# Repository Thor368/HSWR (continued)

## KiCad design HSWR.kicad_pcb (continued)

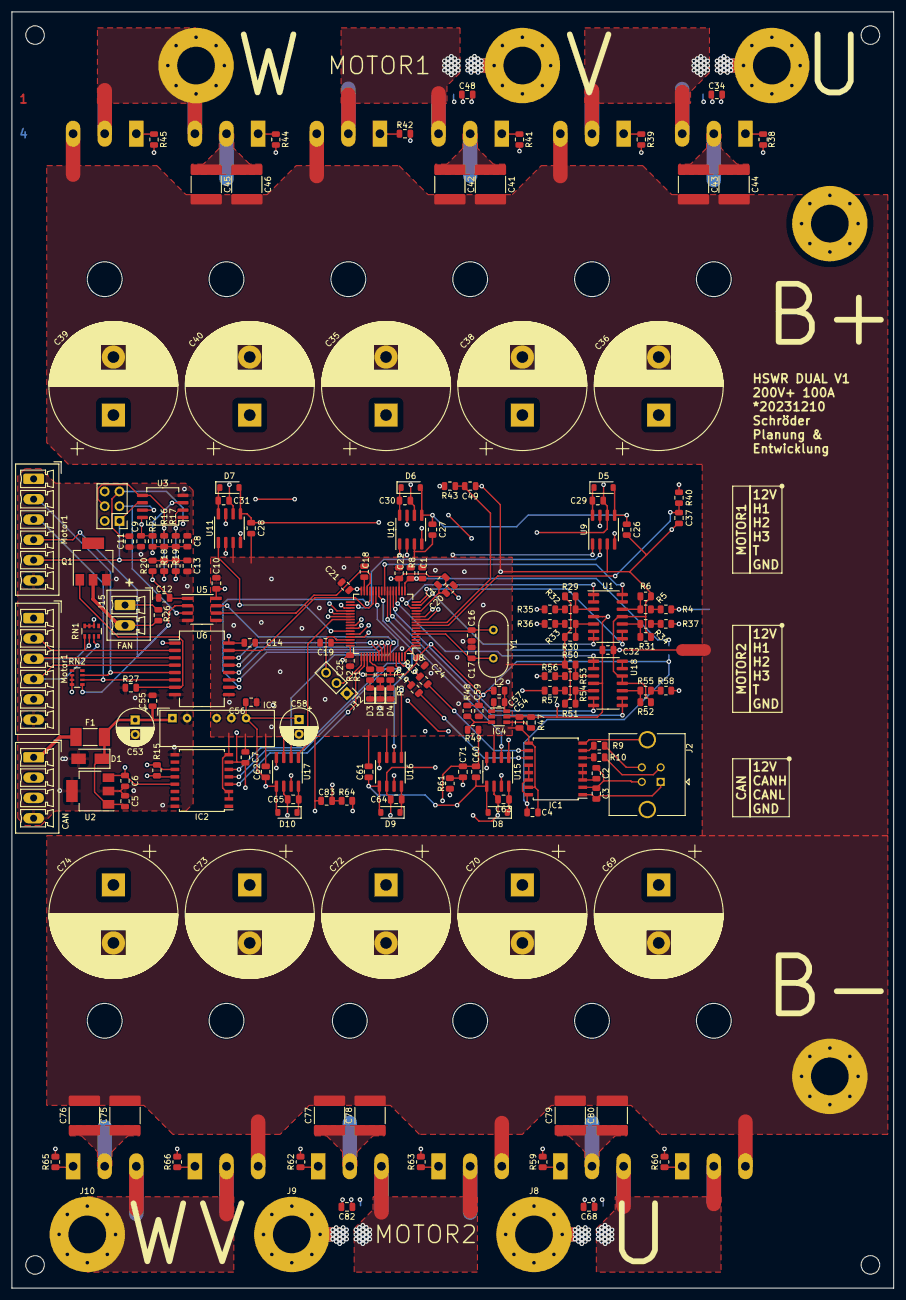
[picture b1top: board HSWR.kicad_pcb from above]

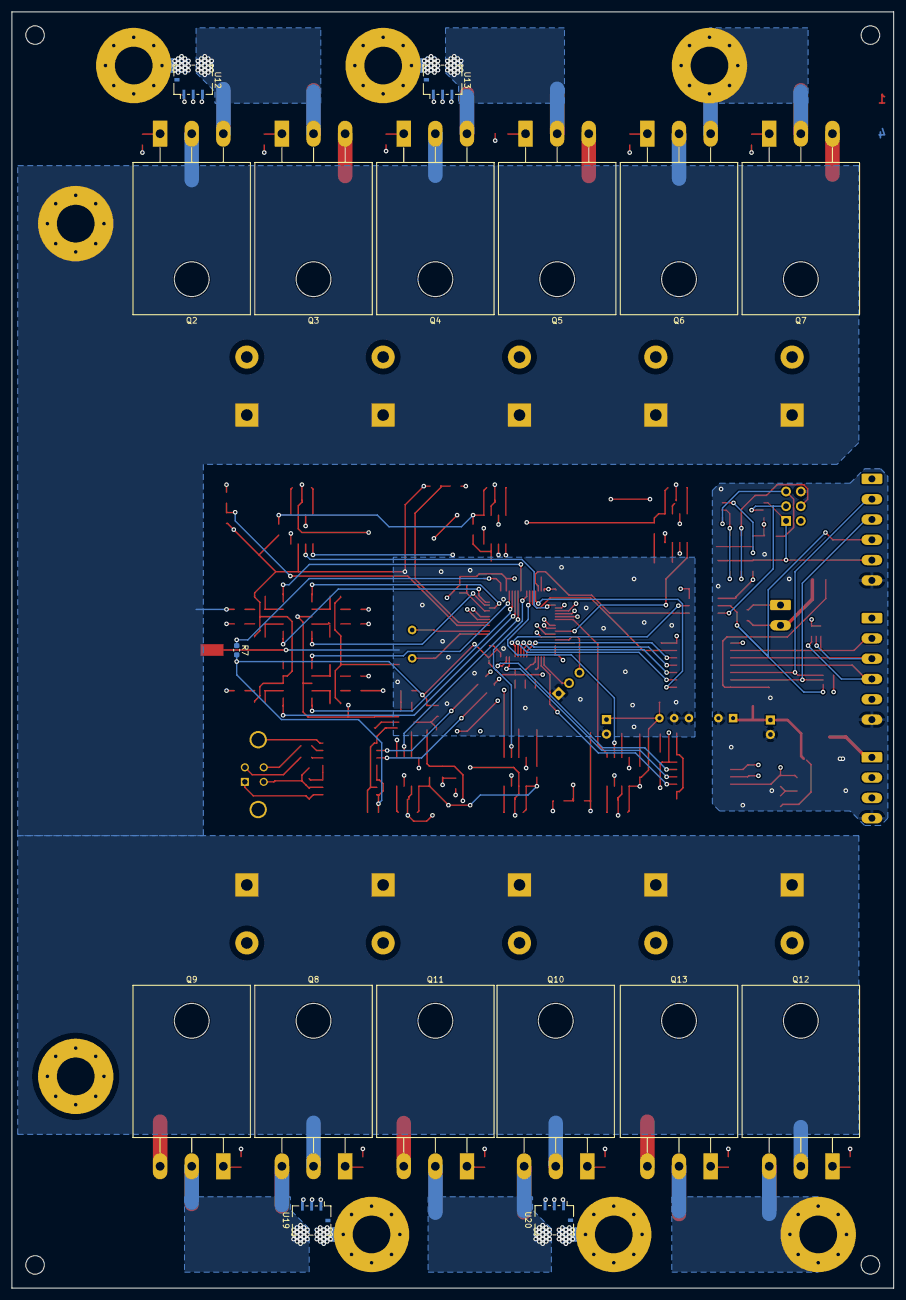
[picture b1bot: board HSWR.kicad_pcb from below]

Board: 4 copper layers, 152.0 x 220.0 mm, 197 parts (17 on the bottom side), 146 nets.

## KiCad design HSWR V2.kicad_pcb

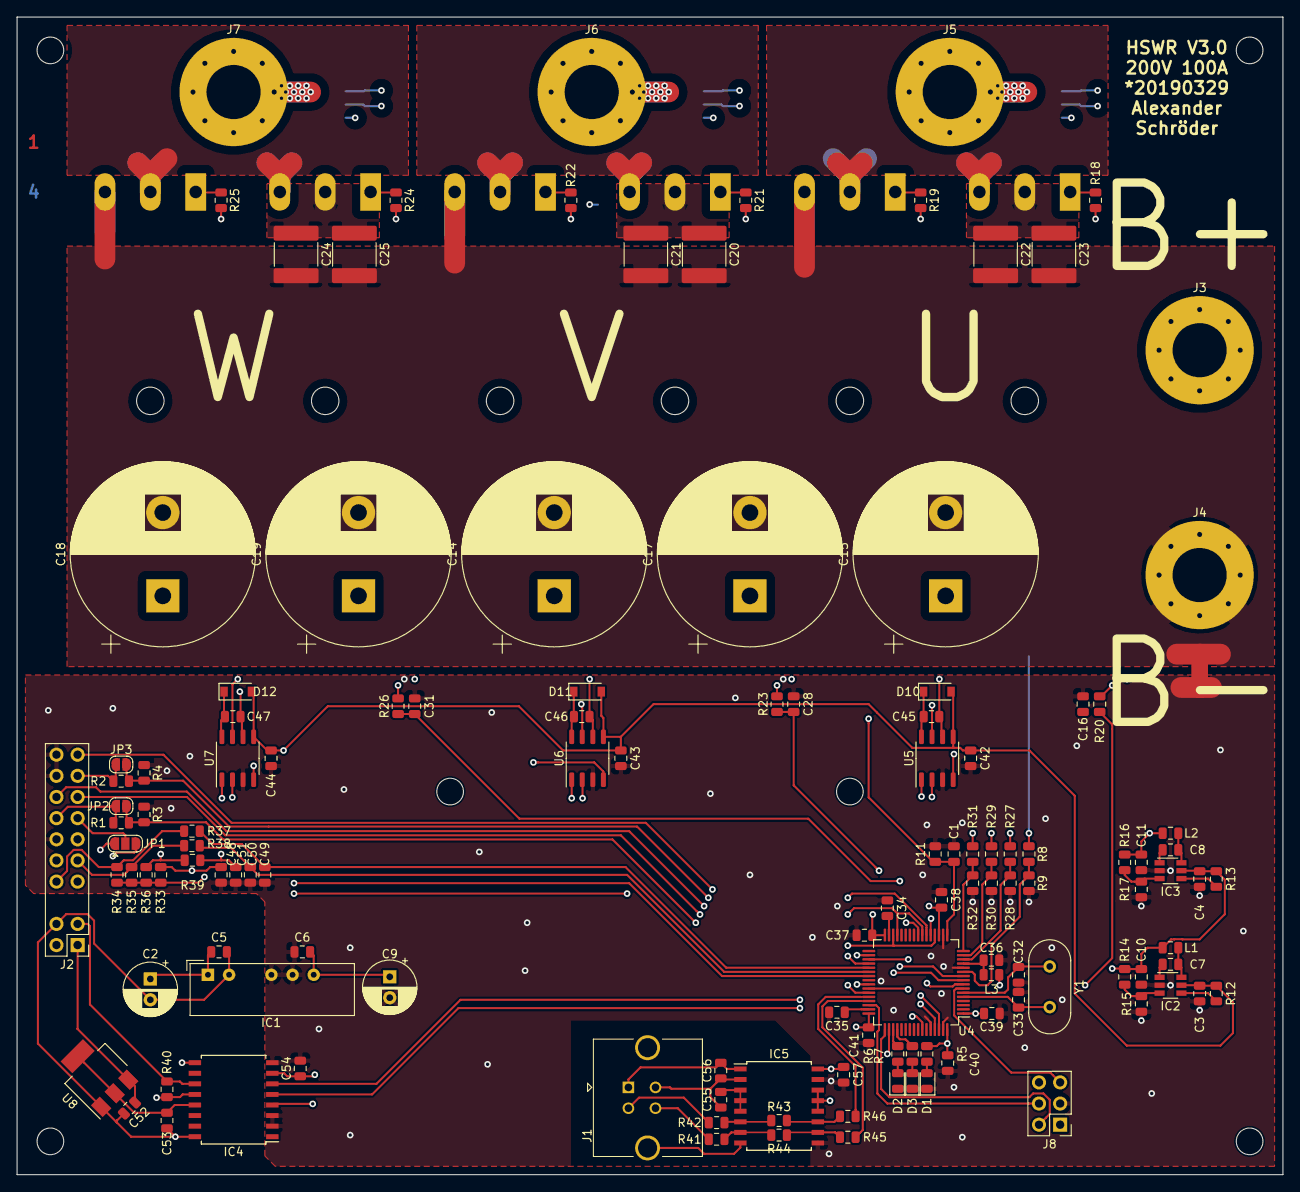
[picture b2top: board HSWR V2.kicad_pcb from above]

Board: 4 copper layers, 152.0 x 139.0 mm, 144 parts (0 on the bottom side), 99 nets.

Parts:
C1, C7, C8, C12, C26, C29, C52, C53, C54, C55, C56, C57: 100n; C_0805_2012Metric
C2, C9: 100u/16V; CP_Radial_D6.3mm_P2.50mm
C3: 22u/16V; C_0805_2012Metric
C4, C10, C11, C36: 22u/6V3; C_0805_2012Metric
C5, C6: 2u2; C_0805_2012Metric
C13, C27, C30, C34, C35, C37, C38, C39, C40, C41, C42, C43, C44, C45, C46, C47: 1u; C_0805_2012Metric
C14, C15, C17, C18, C19: 330u 250V; CP_Radial_D22.0mm_P10.00mm_SnapIn
C16, C28, C31, C48, C49, C50, C51: 4n7; C_0805_2012Metric
C20, C21, C22, C23, C24, C25: 2u2 250V; C_2220_5650Metric
C32, C33: 15p; C_0805_2012Metric
D1, D2, D3: LED; LED_0805_2012Metric
D10, D11, D12: RFN2L4S; D_SOD-123
IC1: B1212S-2W; Converter_DCDC_muRata_NMAxxxxSC_THT
IC2, IC3: JW5052C; TSOT-23-6
IC4: ADUM3054; SOIC-16W_7.5x10.3mm_P1.27mm
IC5: ADuM4160; SOIC-16W_7.5x10.3mm_P1.27mm
J1: USB_B; USB_B_TE_5787834_Vertical
J2: IO; PinHeader_2x10_P2.54mm_Vertical
J3: B+; MountingHole_6.5mm_Pad_Via
J4: B-; MountingHole_6.5mm_Pad_Via
J5: U; MountingHole_6.5mm_Pad_Via
J6: V; MountingHole_6.5mm_Pad_Via
J7: W; MountingHole_6.5mm_Pad_Via
J8: SWD; PinHeader_2x03_P2.54mm_Vertical
JP1: 5V/3V3; SolderJumper-3_P1.3mm_Open_RoundedPad1.0x1.5mm
JP2, JP3: opt.; SolderJumper-2_P1.3mm_Open_RoundedPad1.0x1.5mm
L1, L2: FCI201209F-4R7K; L_0805_2012Metric
L3: 22uH; L_0805_2012Metric
NT1: Net-Tie_2; NetTie-2_SMD_Pad2.0mm
Q1, Q2, Q3, Q4, Q5, Q6: IXFK300N20X3; TO-264-3_Horizontal_TabUp
R1, R2, R20, R23, R26: 1k; R_0805_2012Metric
R3, R4: 1k5; R_0805_2012Metric
R5: 470R; R_0805_2012Metric
R6, R7, R40: 120R; R_0805_2012Metric
R8, R27, R29, R31: 300k 0.1%; R_0805_2012Metric
R9, R28, R30, R32: 4k7 0.1%; R_0805_2012Metric
R10: NTC; R_0603_1608Metric
R11, R33, R37, R38, R39: 10k; R_0805_2012Metric
R12, R13: 100k; R_0805_2012Metric
R14: 110k; R_0805_2012Metric
R15: 15k; R_0805_2012Metric
R16: 49k9; R_0805_2012Metric
R17: 11k; R_0805_2012Metric
R18, R19, R21, R22, R24, R25: 1R; R_0805_2012Metric
R34, R35, R36: 2k2; R_0805_2012Metric
R41, R42, R45, R46: 22R; R_0805_2012Metric
R43, R44: 0R; R_0805_2012Metric
U1, U2, U3: ACS781xLRTR-150B; Allegro_PSOF-7_4.8x6.4mm_P1.60mm
U4: STM32F405RGTx; LQFP-64_10x10mm_P0.5mm
U5, U6, U7: IRS2186; SO-8_3.9x4.9mm_P1.27mm
U8: AP1117-50; SOT-223-3_TabPin2
Y1: 8MHz; Crystal_HC49-U_Vertical

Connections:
+3V3: C11.1, C12.1, C13.2, C26.1, C27.2, C29.1, C30.2, C37.1, C38.1, C39.1, C40.1, C41.1, C54.1, C57.2, IC4.7, IC5.12, IC5.13, IC5.14, IC5.16, J8.1, JP1.1, L2.1, L3.2, R5.2, R10.2, R16.1, R33.2, R34.2, R35.2, R36.2, U1.1, U2.1, U3.1, U4.1, U4.19, U4.32, U4.48, U4.64
+5V: C4.1, C10.1, IC3.5, J2.7, JP1.3, L1.1, R13.2, R14.1
+12V: C3.1, C6.1, C9.1, C42.2, C43.2, C44.2, D10.2, D11.2, D12.2, IC1.6, IC2.5, R12.2, U5.5, U6.5, U7.5
+12VA: C2.1, C5.2, C52.1, IC1.1, J2.1, U8.3
+BATT: C14.1, C15.1, C17.1, C18.1, C19.1, C20.1, C21.1, C22.1, C23.1, C24.1, C25.1, J3.1, Q1.2, Q3.2, Q5.2, R8.1
/CAN bus transceiver/CANH: IC4.12, J2.2, R40.1
/CAN bus transceiver/CANL: IC4.11, J2.3, R40.2
/CAN bus transceiver/CAN_RX: IC4.5, U4.61
/CAN bus transceiver/CAN_TX: IC4.6, U4.62
/Filters/HALL1_IN: J2.10, R36.1, R39.1
/Filters/HALL1_OUT: C51.1, R39.2, U4.39
/Filters/HALL2_IN: J2.9, R35.1, R38.1
/Filters/HALL2_OUT: C50.1, R38.2, U4.38
/Filters/HALL3_IN: J2.8, R34.1, R37.1
/Filters/HALL3_OUT: C49.1, R37.2, U4.37
/Filters/TEMP_IN: C48.1, J2.11, R33.1, U4.24
/MCU/BUS_U: R8.2, R9.1, U4.11
/MCU/CAN_VSS_SENSE: IC4.4, U4.50
/MCU/LED_GREEN: R6.2, U4.51
/MCU/LED_RED: R7.2, U4.52
/MCU/MISO_ADC_EXT2: JP3.2, R2.1, R4.2, U4.22
/MCU/RX_SDA_NSS: J2.15, U4.20, U4.30
/MCU/SCK_ADC_EXT: JP2.2, R1.1, R3.2, U4.21
/MCU/SERVO: J2.19, U4.58
/MCU/TEMP_INT: C1.1, R10.1, R11.2, U4.17
/MCU/TX_SCL_MOSI: J2.16, U4.23, U4.29
/MCU/U_I: C16.1, R20.1, U4.8
/MCU/U_PWM_H: U4.41, U5.1
/MCU/U_PWM_L: U4.34, U5.2
/MCU/U_U: R27.2, R28.1, U4.14
/MCU/V_I: C28.1, R23.1, U4.9
/MCU/V_PWM_H: U4.42, U6.1
/MCU/V_PWM_L: U4.35, U6.2
/MCU/V_U: R29.2, R30.1, U4.15
/MCU/W_I: C31.1, R26.1, U4.10
/MCU/W_PWM_H: U4.43, U7.1
/MCU/W_PWM_L: U4.36, U7.2
/MCU/W_U: R31.2, R32.1, U4.16
/Mosfet driver/U_GH: R18.2, U5.7
/Mosfet driver/U_GL: R19.2, U5.4
/Mosfet driver/U_VP: C45.2, Q1.3, Q2.2, R27.1, U1.5, U5.6
/Mosfet driver/V_GH: R21.2, U6.7
/Mosfet driver/V_GL: R22.2, U6.4
/Mosfet driver/V_VP: C46.2, Q3.3, Q4.2, R29.1, U2.5, U6.6
/Mosfet driver/W_GH: R24.2, U7.7
/Mosfet driver/W_GL: R25.2, U7.4
/Mosfet driver/W_VP: C47.2, Q5.3, Q6.2, R31.1, U3.5, U7.6
/Power MOSFETS/U: J5.1, U1.6
/Power MOSFETS/V: J6.1, U2.6
/Power MOSFETS/W: J7.1, U3.6
/USB/Device_D+: R45.2, U4.45
/USB/Device_D-: R46.1, U4.44
/USB/Host_D+: J1.3, R41.1
/USB/Host_D-: J1.2, R42.2
/USB/VBUS: C56.2, IC5.1, J1.1
Earth: C2.2, C5.1, C52.2, C53.2, IC1.2, IC4.9, IC4.16, J2.4, U8.1
GND: C1.2, C3.2, C4.2, C6.2, C9.2, C10.2, C11.2, C12.2, C13.1, C16.2, C26.2, C27.1, C28.2, C29.2, C30.1, C31.2, C32.1, C33.2, C34.2, C35.2, C36.1, C37.2, C38.2, C39.2, C40.2, C41.2, C42.1, C43.1, C44.1, C48.2, C49.2, C50.2, C51.2, C54.2, C57.1, D1.1, D2.1, D3.1, IC1.4, IC1.5, IC2.2, IC3.2, IC4.2, IC4.3, IC4.8, IC5.9, IC5.15, J2.12, J2.18, J2.20, J8.3, NT1.1, R3.1, R4.1, R9.2, R11.1, R15.2, R17.2, R28.2, R30.2, R32.2, U1.2, U2.2, U3.2, U4.12, U4.18, U4.60, U4.63, U5.3, U6.3, U7.3
GNDD: C55.1, C56.1, IC5.2, IC5.8, J1.4, J1.5
GNDPWR: C14.2, C15.2, C17.2, C18.2, C19.2, C20.2, C21.2, C22.2, C23.2, C24.2, C25.2, J4.1, NT1.2, Q2.3, Q4.3, Q6.3
NRST: J8.5, U4.7
unnamed: C7.1, IC2.1
unnamed: C7.2, IC2.6, L1.2
unnamed: C8.1, IC3.1
unnamed: C8.2, IC3.6, L2.2
unnamed: C32.2, U4.6, Y1.1
unnamed: C33.1, U4.5, Y1.2
unnamed: C34.1, U4.31
unnamed: C35.1, U4.47
unnamed: C36.2, L3.1, U4.13
unnamed: C45.1, D10.1, U5.8
unnamed: C46.1, D11.1, U6.8
unnamed: C47.1, D12.1, U7.8
unnamed: C53.1, IC4.13, U8.2
unnamed: C55.2, IC5.3, IC5.4, IC5.5
unnamed: D1.2, R5.1
unnamed: D2.2, R6.1
unnamed: D3.2, R7.1
unnamed: IC2.3, R14.2, R15.1
unnamed: IC2.4, R12.1
unnamed: IC3.3, R16.2, R17.1
unnamed: IC3.4, R13.1
unnamed: IC5.6, R42.1, R43.1
unnamed: IC5.7, R41.2, R44.2
unnamed: IC5.10, R44.1, R45.1
unnamed: IC5.11, R43.2, R46.2
unnamed: J2.13, JP1.2
unnamed: J2.14, JP2.1, R1.2
unnamed: J2.17, JP3.1, R2.2
unnamed: Q1.1, R18.1
unnamed: Q2.1, R19.1
unnamed: Q3.1, R21.1
unnamed: Q4.1, R22.1
unnamed: Q5.1, R24.1
unnamed: Q6.1, R25.1
unnamed: R20.2, U1.3
unnamed: R23.2, U2.3
unnamed: R26.2, U3.3
SWCLK: J8.2, U4.49
SWDIO: J8.4, U4.46

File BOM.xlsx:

Reference(s) | Value | Footprint
C1, C12, C26, C29, C48, C49, C50, C51, C55, C56, C57, C58, C59 | 100n | Capacitor_SMD:C_0805_2012Metric
C2, C9 | 100u/16V | Capacitor_THT:CP_Radial_D6.3mm_P2.50mm
C3 | 22u/16V | Capacitor_SMD:C_0805_2012Metric
C4, C10, C11, C36 | 22u/6V3 | Capacitor_SMD:C_0805_2012Metric
C5, C6 | 2u2 | Capacitor_SMD:C_0805_2012Metric
C7, C8, C52, C53, C54 | 100n | Capacitor_SMD:C_0805_2012Metric
C13, C27, C30, C34, C35, C37, C38, C39, C40, C41, C42, C43, C44, C45, C46, C47 | 1u | Capacitor_SMD:C_0805_2012Metric
C14, C15, C17, C18, C19 | 330u 250V | Capacitor_THT:CP_Radial_D22.0mm_P10.00mm_SnapIn
C16, C28, C31 | 4n7 | Capacitor_SMD:C_0805_2012Metric
C20, C21, C22, C23, C24, C25 | 2u2 250V | Capacitor_SMD:C_2220_5650Metric
C32, C33 | 15p | Capacitor_SMD:C_0805_2012Metric
D1, D2, D3 | LED | LED_SMD:LED_0805_2012Metric
D10, D11, D12 | RFN2L4S | Diode_SMD:D_SOD-123
IC1 | B1212S-2W | Converter_DCDC:Converter_DCDC_muRata_NMAxxxxSC_THT
IC2, IC3 | JW5052C | Package_TO_SOT_SMD:TSOT-23-6
IC4 | ADUM3054 | Package_SO:SOIC-16W_7.5x10.3mm_P1.27mm
IC5 | ADuM4160 | Package_SO:SOIC-16W_7.5x10.3mm_P1.27mm
J1 | USB_B | Connector_USB:USB_B_TE_5787834_Vertical
J2 | IO | Connector_IDC:IDC-Header_2x08_P2.54mm_Vertical_Lock
J3 | B+ | MountingHole:MountingHole_6.5mm_Pad_Via
J4 | B- | MountingHole:MountingHole_6.5mm_Pad_Via
J5 | U | MountingHole:MountingHole_6.5mm_Pad_Via
J6 | V | MountingHole:MountingHole_6.5mm_Pad_Via
J7 | W | MountingHole:MountingHole_6.5mm_Pad_Via
J8 | SWD | Connector_PinHeader_2.54mm:PinHeader_2x03_P2.54mm_Vertical
J9 | AVR-ISP-6 | Connector_PinSocket_2.54mm:PinSocket_2x03_P2.54mm_Vertical
JP1 | H1 | Jumper:SolderJumper-2_P1.3mm_Open_TrianglePad1.0x1.5mm
JP2 | UART | Jumper:SolderJumper-3_P2.0mm_Open_TrianglePad1.0x1.5mm
JP3 | H2 | Jumper:SolderJumper-2_P1.3mm_Open_TrianglePad1.0x1.5mm
JP4 | H3 | Jumper:SolderJumper-2_P1.3mm_Open_TrianglePad1.0x1.5mm
L1, L2 | FCI201209F-4R7K | Inductor_SMD:L_0805_2012Metric
L3 | 22uH | Inductor_SMD:L_0805_2012Metric
NT1 | Net-Tie_2 | NetTie:NetTie-2_SMD_Pad2.0mm
Q1, Q2, Q3, Q4, Q5, Q6 | IXFK300N20X3 | Package_TO_SOT_THT:TO-264-3_Horizontal_TabUp
Q7 | Q_NMOS_GSD | Package_TO_SOT_SMD:SOT-23
R1, R37 | 100R | Resistor_SMD:R_0805_2012Metric
R2, R20, R23, R26, R36 | 1k | Resistor_SMD:R_0805_2012Metric
R3, R4, R33, R34, R40 | 120R | Resistor_SMD:R_0805_2012Metric
R5 | 470R | Resistor_SMD:R_0805_2012Metric
R6, R7 | 120R | Resistor_SMD:R_0805_2012Metric
R8, R27, R29, R31 | 300k 0.1% | Resistor_SMD:R_0805_2012Metric
R9, R28, R30, R32 | 4k7 0.1% | Resistor_SMD:R_0805_2012Metric
R10 | NTC | Resistor_SMD:R_0603_1608Metric
R11, R35 | 10k | Resistor_SMD:R_0805_2012Metric
R12, R13 | 100k | Resistor_SMD:R_0805_2012Metric
R14 | 110k | Resistor_SMD:R_0805_2012Metric
R15 | 15k | Resistor_SMD:R_0805_2012Metric
R16 | 49k9 | Resistor_SMD:R_0805_2012Metric
R17 | 11k | Resistor_SMD:R_0805_2012Metric
R18, R19, R21, R22, R24, R25 | 1R | Resistor_SMD:R_0805_2012Metric
R41, R42, R45, R46 | 22R | Resistor_SMD:R_0805_2012Metric
R43, R44 | 0R | Resistor_SMD:R_0805_2012Metric
U1, U2, U3 | ACS781xLRTR-150B | Sensor_Current:Allegro_PSOF-7_4.8x6.4mm_P1.60mm
U4 | STM32F405RGTx | Package_QFP:LQFP-64_10x10mm_P0.5mm
U5, U6, U7 | IRS2186 | Package_SO:SO-8_3.9x4.9mm_P1.27mm
U8 | AP1117-50 | Package_TO_SOT_SMD:SOT-223-3_TabPin2
U9 | ATtiny13A-SU | Package_SO:SOIJ-8_5.3x5.3mm_P1.27mm
U10 | AM26LV32xD | Package_SO:SOIC-16_3.9x9.9mm_P1.27mm
U11, U12 | ADuM120N | Package_SO:SOIC-8_3.9x4.9mm_P1.27mm
U13 | PC355 | Package_SO:SO-4_4.4x4.3mm_P2.54mm
Y1 | 8MHz | Crystal:Crystal_HC49-U_Vertical

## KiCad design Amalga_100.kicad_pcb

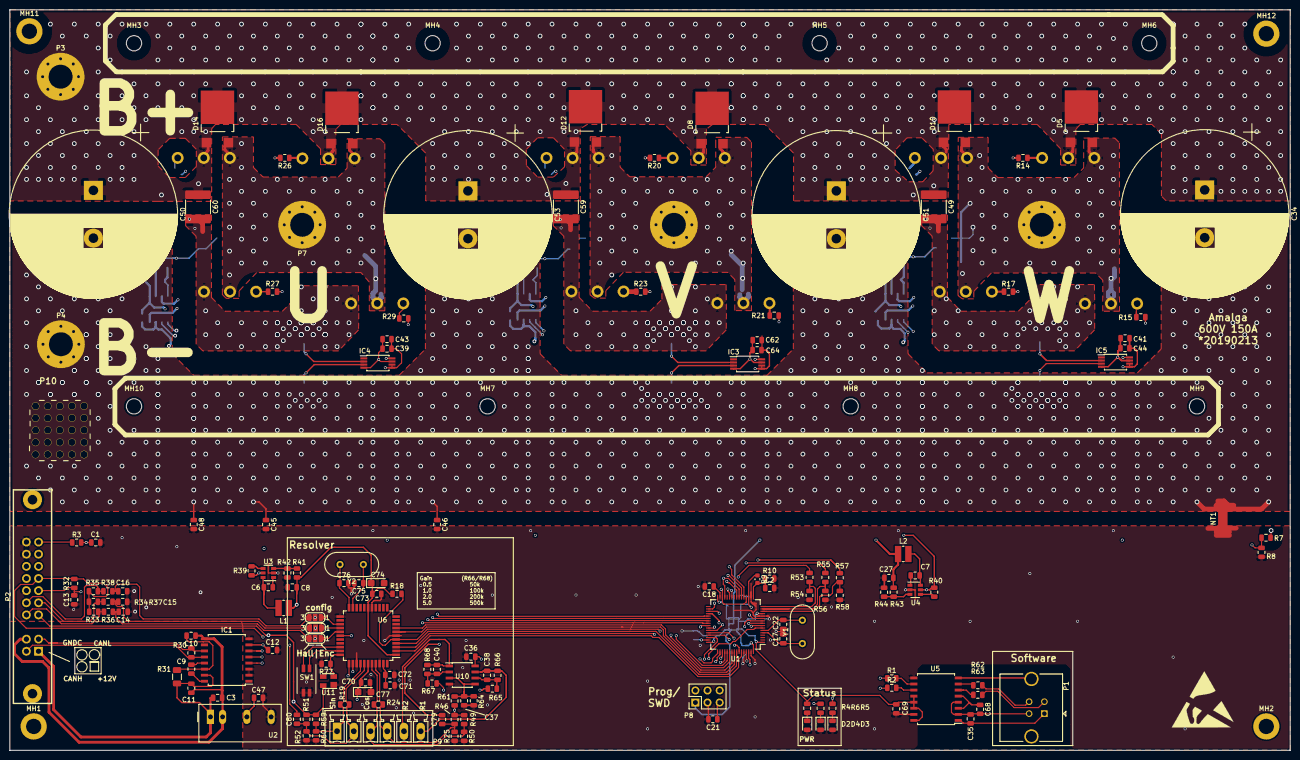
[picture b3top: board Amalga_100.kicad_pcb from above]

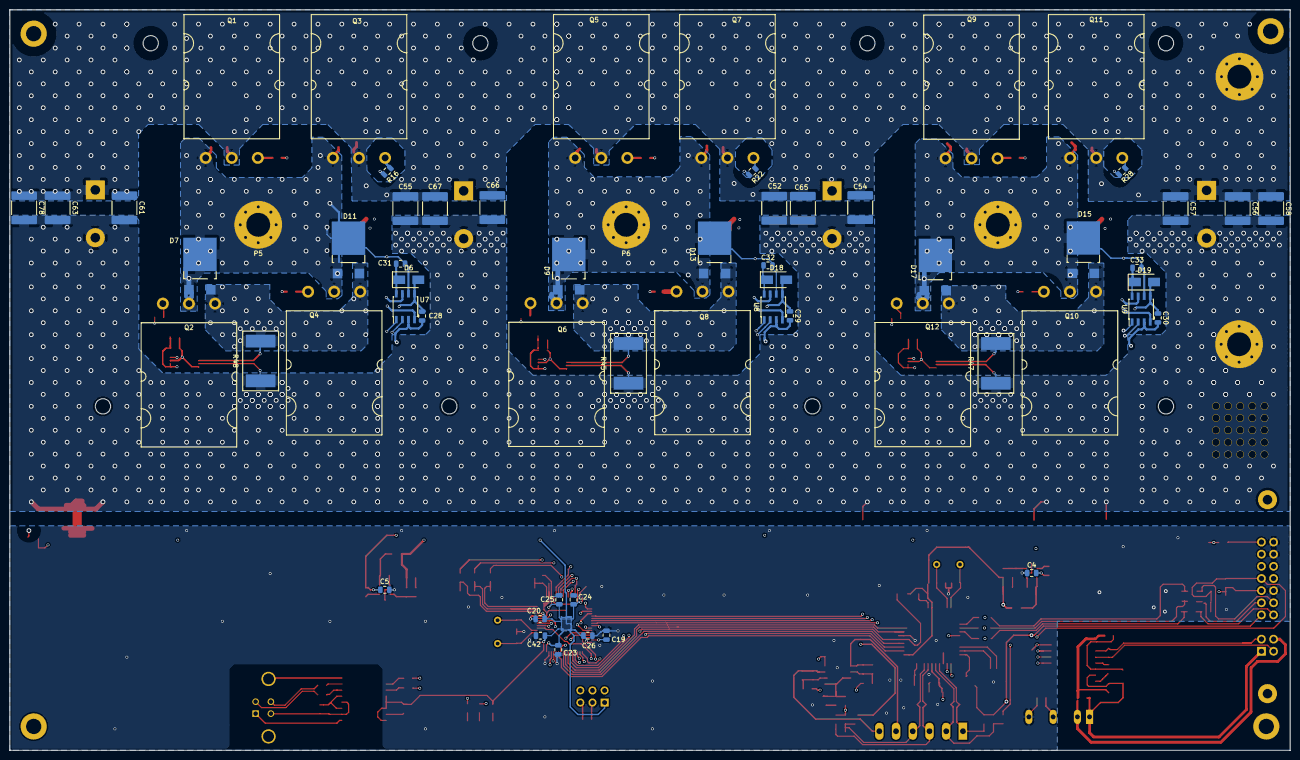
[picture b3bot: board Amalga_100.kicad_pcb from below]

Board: 6 copper layers, 268.0 x 155.0 mm, 223 parts (59 on the bottom side), 133 nets.

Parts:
C1, C2, C6, C7, C11, C12, C35, C45, C46, C48, C68, C69: 100n; C_0805_2012Metric
C3, C47: 2u2; C_0805_2012Metric
C4, C5, C8, C27: 22u; C_0805_2012Metric
C9, C18, C19, C20, C23, C24, C25, C26, C28, C29, C30, C42, C43, C44, C64: 1u; C_0805_2012Metric
C10: 10u; C_0805_2012Metric
C13, C14, C15, C16: 4n7; C_0805_2012Metric
C17, C22: 15p; C_0805_2012Metric
C21, C39, C41, C62: 10n; C_0805_2012Metric
C31, C32, C33: 1u 600V; C_0805_2012Metric
C34, C50, C51, C53: 470u 600V; CP_Radial_D35.0mm_P10.00mm_SnapIn
C36, C37: 100nF; C_0805_2012Metric
C38, C40: 120pF; C_0805_2012Metric
C49, C52, C54, C55, C56, C57, C58, C59, C60, C61, C63, C65, C66, C67, C78: 1u 600V; C_2220_5650Metric
C70, C72, C73: 10nF; C_0805_2012Metric
C71: 10uF; C_0805_2012Metric
C74, C77: 4.7uF; CP_EIA-3216-12_Kemet-S
C75, C76: 20pF; C_0805_2012Metric
C79, C80: 1uF; C_0805_2012Metric
D2: LED; LED_0805_2012Metric
D3: GREEN; LED_0805_2012Metric
D4: RED; LED_0805_2012Metric
D5, D7, D8, D9, D10, D11, D12, D13, D14, D15, D16, D17: CDBDSC10650-G; TO-252-2_TabPin1
D6, D18, D19: RFN2L4S; D_SMA
IC1: ADM3052; SOIC-16W_7.5x10.3mm_P1.27mm
IC3, IC4, IC5: INA240A1; TSSOP-8_4.4x3mm_P0.65mm
JP1, JP2, JP3: SolderJumper_3_Bridged12; SolderJumper-3_P1.3mm_Open_RoundedPad1.0x1.5mm_NumberLabels
L1, L2: 4.7uH; L_Wuerth_MAPI-3020
MH1, MH2, MH11, MH12: MountingHole; MountingHole_3.2mm_M3_ISO14580_Pad
MH3, MH4, MH5, MH6, MH7, MH8, MH9, MH10: MountingHole; MountingHole_3.2mm_M3_ISO14580
NT1: Net-Tie_2; NetTie-2_SMD_Pad2.0mm
P1: USB_B; USB_B_TE_5787834_Vertical
P2: Interface; XG4A_20_wo_56
P3: IN+; MountingHole_5mm_Pad_Via
P4: IN-; MountingHole_5mm_Pad_Via
P5: MOTOR3; MountingHole_5mm_Pad_Via
P6: MOTOR2; MountingHole_5mm_Pad_Via
P7: MOTOR1; MountingHole_5mm_Pad_Via
P8: SWD; PinHeader_2x03_P2.54mm_Vertical
P9: CONN_6-HSWR-V2-rescue; PhoenixContact_MCV_1,5_6-G-3.5_1x06_P3.50mm_Vertical
P10: IN-; redcube_250A_2
Q1, Q2, Q3, Q4, Q5, Q6, Q7, Q8, Q9, Q10, Q11, Q12: IRFP4668PBF; TO-264_flat_reverse_2
R1, R2, R62, R63: 22R; R_0805_2012Metric
R3, R4, R33, R34, R35: 2k2; R_0805_2012Metric
R5, R6, R30: 120R; R_0805_2012Metric
R7, R53, R55, R57: 220k; R_0805_2012Metric
R8, R54, R56, R58: 3k3; R_0805_2012Metric
R9: NTC 10k; R_0603_1608Metric
R10, R18, R32, R36, R37, R38, R77: 10k; R_0805_2012Metric
R14, R15, R16, R17, R20, R21, R22, R23, R26, R27, R28, R29: 1R; R_0805_2012Metric
R19, R24: 68k; R_0805_2012Metric
R25, R46, R49, R50, R51, R52, R59, R60: 50k; R_0805_2012Metric
R31: 300R; R_1206_3216Metric
R39: 28k; R_0805_2012Metric
R40: 100k; R_0805_2012Metric
R41: 110k; R_0805_2012Metric
R42: 15k; R_0805_2012Metric
R43: 49k9; R_0805_2012Metric
R44: 11k; R_0805_2012Metric
R45, R47, R48: CSS2H-3920R-L500; CSS3920
R61: 442R 1%; R_0805_2012Metric
R64: 1K24 1%; R_0805_2012Metric
R65, R67: 100k 1%; R_0805_2012Metric
R66, R68: 25k 1%; R_0805_2012Metric
SW1: SW_DIP_x02; SW_DIP_x2_W5.08mm_Slide_Copal_CHS-A
SYM1: SYM_ESD_Small; ESD-Logo_13.2x12mm_SilkScreen
U1: STM32F40X_LQFP64; LQFP-64_10x10mm_P0.5mm
U2: B1215S-2W; Converter_DCDC_TRACO_TMR-1-xxxx_Single_THT
U3, U4: JW5052C; SOT-23-6
U5: ADUM3160; SOIC-16W_7.5x10.3mm_P1.27mm
U6: AD2S1205; LQFP-44_10x10mm_P0.8mm
U7, U8, U9: IRS2186; SOIC-8_3.9x4.9mm_P1.27mm
U10: AD8397; SOIC-8_3.9x4.9mm_P1.27mm
U11: ADM811; SOT-143
Y1: 8MHz; Crystal_HC49-U_Vertical
Y2: 8.912 MHZ; Crystal_HC49-U_Vertical

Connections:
+3V3: C12.1, C20.2, C23.2, C24.2, C25.2, C26.2, C27.2, C39.1, C41.1, C42.2, C43.1, C44.1, C62.1, C64.1, C69.1, IC1.7, IC3.5, IC3.6, IC4.5, IC4.6, IC5.5, IC5.6, L2.1, P2.13, P8.1, R4.2, R9.1, R32.2, R33.2, R34.2, R35.2, R43.2, U1.1, U1.13, U1.19, U1.32, U1.48, U1.64, U5.12, U5.13, U5.14, U5.16
+5V: C8.2, C70.1, C73.1, C74.1, C77.1, L1.1, P2.7, R18.1, R41.2, R46.1, R49.1, R51.1, R59.1, R61.2, U6.1, U6.17, U6.39, U11.4
+12VA: C3.1, C11.1, IC1.15, P2.1, R31.2, U2.1
+15V: C4.2, C5.2, C28.1, C29.1, C30.1, C36.1, C47.1, D6.2, D18.2, D19.2, R39.2, R40.2, U2.4, U3.5, U4.5, U7.5, U8.5, U9.5, U10.8
+BATT: C34.1, C49.1, C50.1, C51.1, C52.1, C53.1, C54.1, C55.1, C56.1, C57.1, C58.1, C59.1, C60.1, C61.1, C63.1, C65.1, C66.1, C67.1, C78.1, D5.1, D8.1, D10.1, D12.1, D14.1, D16.1, P3.1, Q1.2, Q3.2, Q5.2, Q7.2, Q9.2, Q11.2, R7.1
/CAN bus transceiver/CANH: IC1.12, P2.2, R30.1
/CAN bus transceiver/CANL: IC1.11, P2.3, R30.2
/CAN bus transceiver/CAN_RX: IC1.5, U1.61
/CAN bus transceiver/CAN_TX: IC1.6, U1.62
/Filters/HALL1_IN: P2.10, R35.1, R38.1
/Filters/HALL1_OUT: C16.1, JP3.3, R38.2
/Filters/HALL2_IN: P2.9, R34.1, R37.1
/Filters/HALL2_OUT: C15.1, JP2.3, R37.2
/Filters/HALL3_IN: P2.8, R33.1, R36.1
/Filters/HALL3_OUT: C14.1, JP1.3, R36.2
/Filters/TEMP_IN: C13.2, P2.11, R32.1, U1.24
/MCU/BR_SO1: IC4.8, U1.8
/MCU/BR_SO2: IC5.8, U1.9
/MCU/BR_SO3: IC3.8, U1.10
/MCU/CAN_VSS_Sense: IC1.4, U1.50
/MCU/H1_pwm: U1.43, U7.1
/MCU/H2_pwm: U1.42, U8.1
/MCU/H3_pwm: U1.41, U9.1
/MCU/HALL_1: JP3.2, U1.37
/MCU/HALL_2: JP2.2, U1.38
/MCU/HALL_3: JP1.2, U1.39
/MCU/L1_pwm: U1.36, U7.2
/MCU/L2_pwm: U1.35, U8.2
/MCU/L3_pwm: U1.34, U9.2
/MCU/LED_GREEN: R5.2, U1.51
/MCU/LED_RED: R6.2, U1.52
/MCU/MISO_ADC_EXT2: P2.17, U1.22
/MCU/RX_SDA_NSS: P2.16, U1.20, U1.30
/MCU/SCK_ADC_EXT: P2.14, U1.21
/MCU/SENS1: R53.2, R54.2, U1.16
/MCU/SENS2: R55.2, R56.2, U1.15
/MCU/SENS3: R57.2, R58.2, U1.14
/MCU/SERVO: C1.2, R3.2, U1.58
/MCU/TX_SCL_MOSI: P2.15, U1.23, U1.29
/MCU/Temp_Platine: C2.1, R9.2, R10.1, U1.17
/MCU/U_Bat: R7.2, R8.1, U1.11
/Mosfet driver/H1_LOW: C49.2, D7.2, D11.2, IC5.2, Q2.3, Q4.3, R48.2
/Mosfet driver/H1_out: R14.2, R16.2, U7.7
/Mosfet driver/H2_LOW: C59.2, D9.2, D13.2, IC3.2, Q6.3, Q8.3, R45.2
/Mosfet driver/H2_out: R20.2, R22.2, U8.7
/Mosfet driver/H3_LOW: C60.2, D15.2, D17.2, IC4.2, Q10.3, Q12.3, R47.2
/Mosfet driver/H3_out: R26.2, R28.2, U9.7
/Mosfet driver/L1_out: R15.2, R17.2, U7.4
/Mosfet driver/L2_out: R21.2, R23.2, U8.4
/Mosfet driver/L3_out: R27.2, R29.2, U9.4
/Resolver/*CS: U1.54, U6.3
/Resolver/*RDvel: R18.2, U1.53, U6.5
/Resolver/Buffer Circuit R2D/*EXC: R65.2, U6.35
/Resolver/Buffer Circuit R2D/EXC: R67.2, U6.34
/Resolver/Buffer Circuit R2D/offset_op: C37.1, R61.1, R64.2, U10.3, U10.5
/Resolver/Cos(S2): C79.1, P9.4, R24.2, R25.1, R46.2, U6.41
/Resolver/CosLO(S6): P9.3, R24.1, R49.2, R50.1, U6.40
/Resolver/R1: C38.2, P9.6, R66.2, U10.7
/Resolver/R2: C40.2, P9.5, R68.2, U10.1
/Resolver/RD: U1.59, U6.2
/Resolver/Sin(S1): P9.1, R19.1, R59.2, R60.1, U6.37
/Resolver/SinLO(S3): C80.1, P9.2, R19.2, R51.2, R52.1, U6.38
/USB-Isolator/DD+: R1.1, U1.45
/USB-Isolator/DD-: R2.1, U1.44
/USB-Isolator/GND1: C35.2, C68.2, P1.4, P1.5, U5.2, U5.4, U5.8
/USB-Isolator/UD+: P1.3, R62.2
/USB-Isolator/UD-: P1.2, R63.2
/USB-Isolator/VBUS1: C35.1, P1.1, U5.1
A(enc): JP3.1, U6.25
B(enc): JP2.1, U6.26
COS_analog_RES: C79.2, U1.27
Earth: C3.2, C10.1, C11.2, IC1.9, P2.4, U2.2
GND: C1.1, C2.2, C4.1, C5.1, C8.1, C12.2, C13.1, C14.2, C15.2, C16.2, C17.2, C18.2, C19.2, C20.1, C21.1, C22.2, C23.1, C24.1, C25.1, C26.1, C27.1, C28.2, C29.2, C30.2, C36.2, C37.2, C39.2, C41.2, C42.1, C43.2, C44.2, C45.2, C46.2, C47.2, C48.2, C62.2, C64.2, C69.2, C70.2, C71.2, C72.2, C73.2, C74.2, C75.2, C76.2, C77.2, D2.2, D3.2, D4.2, IC1.2, IC1.3, IC1.8, IC3.4, IC3.7, IC4.4, IC4.7, IC5.4, IC5.7, NT1.1, P2.12, P2.18, P2.20, P8.3, R8.2, R10.2, R25.2, R42.1, R44.1, R50.2, R52.2, R54.1, R56.1, R58.1, R60.2, R64.1, R77.2, SW1.3, SW1.4, U1.12, U1.18, U1.60, U1.63, U2.6, U3.2, U4.2, U5.9, U5.15, U6.6, U6.16, U6.23, U6.36, U6.42, U7.3, U8.3, U9.3, U10.4, U11.1
GNDPWR: C34.2, C45.1, C46.1, C48.1, C50.2, C51.2, C52.2, C53.2, C54.2, C55.2, C56.2, C57.2, C58.2, C61.2, C63.2, C65.2, C66.2, C67.2, C78.2, IC3.3, IC4.3, IC5.3, NT1.2, P4.1, P10.1, R45.1, R47.1, R48.1
H1_VS: C31.2, D5.2, D7.1, D10.2, D11.1, P5.1, Q1.3, Q2.2, Q3.3, Q4.2, R57.1, U7.6
H2_VS: C32.2, D8.2, D9.1, D12.2, D13.1, P6.1, Q5.3, Q6.2, Q7.3, Q8.2, R55.1, U8.6
H3_VS: C33.2, D14.2, D15.1, D16.2, D17.1, P7.1, Q9.3, Q10.2, Q11.3, Q12.2, R53.1, U9.6
NM(enc): JP1.1, U6.27
NRST: C21.2, P8.5, U1.7
unnamed: C6.1, L1.2, U3.6
unnamed: C6.2, U3.1
unnamed: C7.1, L2.2, U4.6
unnamed: C7.2, U4.1
unnamed: C9.1, IC1.13
unnamed: C9.2, IC1.16
unnamed: C10.2, IC1.14, R31.1
unnamed: C17.1, U1.5, Y1.1
unnamed: C18.1, U1.31
unnamed: C19.1, U1.47
unnamed: C22.1, U1.6, Y1.2
unnamed: C31.1, D6.1, U7.8
unnamed: C32.1, D18.1, U8.8
unnamed: C33.1, D19.1, U9.8
unnamed: C38.1, R65.1, R66.1, U10.6
unnamed: C40.1, R67.1, R68.1, U10.2
unnamed: C68.1, U5.3, U5.5
unnamed: C71.1, C72.1, U6.43
unnamed: C75.1, U6.21, Y2.1
unnamed: C76.1, U6.22, Y2.2
unnamed: D2.1, R4.1
unnamed: D3.1, R5.1
unnamed: D4.1, R6.1
unnamed: P2.19, R3.1
unnamed: Q1.1, R14.1
unnamed: Q2.1, R15.1
unnamed: Q3.1, R16.1
unnamed: Q4.1, R17.1
unnamed: Q5.1, R20.1
unnamed: Q6.1, R21.1
unnamed: Q7.1, R22.1
unnamed: Q8.1, R23.1
unnamed: Q9.1, R26.1
unnamed: Q10.1, R27.1
unnamed: Q11.1, R28.1
unnamed: Q12.1, R29.1
unnamed: R1.2, U5.10
unnamed: R2.2, U5.11
unnamed: R39.1, U3.4
unnamed: R40.1, U4.4
unnamed: R41.1, R42.2, U3.3
unnamed: R43.1, R44.2, U4.3
unnamed: R62.1, U5.7
unnamed: R63.1, U5.6
unnamed: R77.1, U6.33, U11.2
unnamed: SW1.1, U6.32
unnamed: SW1.2, U6.31
SIN_analog_RES: C80.2, U1.26
SPI1_MISO(R2D): U1.56, U6.7
SPI1_MOSI(R2D): U1.57, U6.4
SPI1_SCK_(R2D): U1.55, U6.8
SWCLK: P8.2, U1.49
SWDIO: P8.4, U1.46
dir(enc): U1.40, U6.28

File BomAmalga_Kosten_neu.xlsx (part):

|  |  |  |  |  |  |  |  |  | Bauteile 1 x Platine komp | 775.77000000000021
 |  |  |  |  |  |  |  |  |  | Zus. Komp. 1 x 600V | #REF!
 |  |  |  |  |  |  |  |  |  | Unterschiedliche Bestückung 150V / 600V
 |  |  |  |  |  |  |  |  |  | IGBT 600V |  | Mosfet 150V
 |  |  |  |  |  |  |  |  |  | Digikey Nummer | Preis/Stck | Digikey Nummer | Preis/Stck
Column1 | Column2 | Column3 | Column4 | Column5 | Column7 | Column8 |  | Preis/Platine
Ref | Qnty | Value | Cmp name | Footprint | Vendor
C4, C8, C5, C27, | 4 | 22uF | C-Device | Capacitor_SMD:C_0805_2012Metric | 490-10749-1-ND |  |  | 0
C9, C44, C43, C64, C28, C29, C30, C19, C18, C20, C23, C24, C25, C26, C42, C31, 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 | 20 | 1uF | C-RESCUE-BLDC_4-HSWR-V2-rescue | Capacitor_SMD:C_0805_2012Metric | 1276-1066-1-ND |  |  | 0
C10, | 1 | 10uF | C_Small-Device | Capacitor_SMD:C_0805_2012Metric | 1276-2891-1-ND | 0.22 |  | 0.22
C14, C15, C16, C13, | 4 | 4n7 | C-RESCUE-BLDC_4-HSWR-V2-rescue | Capacitor_SMD:C_0805_2012Metric | 1276-2519-1-ND |  |  | 0
C17, C22, | 2 | 15p | C-RESCUE-BLDC_4-HSWR-V2-rescue | Capacitor_SMD:C_0805_2012Metric | 732-7815-1-ND | 3.6999999999999998E-2 |  | 7.3999999999999996E-2
C36, C37,C45, C46, C48, C1, C2, C11, C12, C6, C7, C68, C69, C35 | 14 | 100nF | C_Small-Device | Capacitor_SMD:C_0805_2012Metric | 1276-1090-1-ND | 0.04 |  | 0.56000000000000005
C38, C40, | 2 | 120pF | C_Small-Device | Capacitor_SMD:C_0805_2012Metric | 311-4190-1-ND |  |  | 0
C41, C39, C62, C21, | 4 | 10nF | C-RESCUE-BLDC_4-HSWR-V2-rescue | Capacitor_SMD:C_0805_2012Metric | 399-17422-1-ND |  |  | 0
C47, C3, | 2 | 2u2 | C-Device | Capacitor_SMD:C_0805_2012Metric | 1276-1162-6-ND | 0.12 |  | 0.24
C51, C53, C50, C34, | 4 | 470u 600V | CP-Device | Capacitor_THT:CP_Radial_D35.0mm_P10.00mm_SnapIn | s.r. |  |  | 0 | X | 493-14693-ND | 8.8000000000000007 | 493-2627-ND | 2.4
C52, C54, C57, C58, C55, C56, C65, C66, C67, C49, C59, C60, C61, C78, C63, | 15 | 1u 600V | C-Device | Capacitor_SMD:C_2220_5650Metric | s.r. | 4.32 |  | 64.800000000000011 | X | 445-7110-1-ND | 3.9 | 445-7950-1-ND | 3
C71, | 1 | 10uF | C_Small-Device | Capacitor_SMD:C_0805_2012Metric | 1276-6456-1-ND | 0.18 |  | 0.18
C72, C70, C73, | 3 | 10nF | C_Small-Device | Capacitor_SMD:C_0805_2012Metric | 1276-2434-1-ND |  |  | 0
C76, C75, | 2 | 20pF | C_Small-Device | Capacitor_SMD:C_0805_2012Metric | 311-4194-1-NDv | 0.09 |  | 0.18
C77, C74, | 2 | 4.7uF | CP1_Small-Device | Capacitor_Tantalum_SMD:CP_EIA-3216-12_Kemet-S | 478-11183-1-ND | 0.2 |  | 0.4
D2, | 1 | LED | LED-RESCUE-BLDC_4-HSWR-V2-rescue | LED_SMD:LED_0805_2012Metric | 732-4982-1-ND |  |  | 0
D3, | 1 | GREEN | LED-RESCUE-BLDC_4-HSWR-V2-rescue | LED_SMD:LED_0805_2012Metric | 732-4986-1-ND |  |  | 0
D4, | 1 | RED | LED-RESCUE-BLDC_4-HSWR-V2-rescue | LED_SMD:LED_0805_2012Metric | 732-4984-1-ND |  |  | 0
D6, D18, D19, | 3 | UA1MTR | D_Small-Device | Diode_SMD:D_SMA | 1655-1690-1-ND | 0.44 |  | 1.32
D10, D11, D12, D14, D15, D13, D5, D7, D8, D9, D16, D17, | 12 | CDBDSC10650-G | D_Schottky-Device | Package_TO_SOT_SMD:TO-252-2_TabPin1 | 641-1928-ND | 3.73 |  | 44.76
IC1, | 1 | ADM3052 | ADM3052-HSWR-V2-rescue | Package_SO:SOIC-16W_7.5x10.3mm_P1.27mm | ADM3052BRWZ-REEL7CT-ND | 7.86 |  | 7.86
IC5, IC4, IC3, | 3 | INA240AX | INA240-HSWR-V2-rescue | Package_SO:TSSOP-8_4.4x3mm_P0.65mm | s.r. | 2.35 |  | 7.0500000000000007 | X | 296-51174-1-ND‎ |  | ?X
JP3, JP1, JP2, | 3 | SolderJumper_3_Bridged12 | SolderJumper_3_Bridged12 | Jumper:SolderJumper-3_P1.3mm_Open_RoundedPad1.0x1.5mm_NumberLabels |  |  |  | 0
L1, L2, | 2 | 4.7uH | INDUCTOR-HSWR-V2-rescue | Inductors_SMD:L_Wuerth_MAPI-3020 | 1276-6218-1-ND | 0.25 |  | 0.5
MH2, MH1, MH12, MH11, | 4 | MountingHole | MountingHole-Mechanical | Mounting_Holes:MountingHole_3.2mm_M3_ISO14580_Pad |  |  |  | 0
MH8, MH5, MH6, MH7, MH10, MH3, MH4, MH9, | 8 | MountingHole | MountingHole-Mechanical | Mounting_Holes:MountingHole_3.2mm_M3_ISO14580 |  |  |  | 0
NT1, | 1 | Net-Tie_2 | Net-Tie_2-Device | NetTie:NetTie-2_SMD_Pad2.0mm |  |  |  | 0
P1, | 1 | USB_B | USB_B-RESCUE-HSWR_V2-HSWR-V2-rescue | Connector_USB:USB_B_TE_5787834_Vertical | 952-1767-ND | 0.8 |  | 0.8
P2, | 1 | Interface | CONN_01X18_20-HSWR-V2-rescue | alexmod:XG4A_20_wo_56 | OR885-ND | 1.43 |  | 1.43
P3, | 1 | IN+ | CONN_1-HSWR-V2-rescue | Mounting_Holes:MountingHole_5mm_Pad_Via | broaching stud m5 |  |  | 0
P4, | 1 | IN- | CONN_1-HSWR-V2-rescue | Mounting_Holes:MountingHole_5mm_Pad_Via | broaching stud m5 |  |  | 0
P5, | 1 | MOTOR3 | CONN_1-HSWR-V2-rescue | Mounting_Holes:MountingHole_5mm_Pad_Via | broaching stud m5 |  |  | 0
P6, | 1 | MOTOR2 | CONN_1-HSWR-V2-rescue | Mounting_Holes:MountingHole_5mm_Pad_Via | broaching stud m5 |  |  | 0
P7, | 1 | MOTOR1 | CONN_1-HSWR-V2-rescue | Mounting_Holes:MountingHole_5mm_Pad_Via | broaching stud m5 |  |  | 0
P8, | 1 | SWD | CONN_6-HSWR-V2-rescue | Connector_PinHeader_2.54mm:PinHeader_2x03_P2.54mm_Vertical | 732-5394-N | 0.45 |  | 0.45
P9, | 1 | CONN_6-HSWR-V2-rescue | CONN_6-HSWR-V2-rescue | Connector_Phoenix_MC:PhoenixContact_MCV_1,5_6-G-3.5_1x06_P3.50mm_Vertical | 277-5735-ND |  |  | 0
P10, | 1 | IN- | CONN_1-HSWR-V2-rescue | eigene_mod:redcube_250A_2 |  |  |  | 0
Q12, Q11, Q8, Q7, Q4, Q3, Q1, Q2, Q5, Q6, Q9, Q10, | 12 | IRFP4668PBF | Q_NMOS_GDS-Device | eigene_mod:TO-264_flat_reverse_2 | s.r. | 16.03 |  | 192.36 | X | IXXK200N65B4-ND | 15.2 | IXFK360N15T2-ND | 16.03
R2, R1, R62, R63, | 4 | 22R | R-Device | Resistor_SMD:R_0805_2012Metric | A126437CT-ND |  |  | 0
R3, R4, R33, R34, R35, | 5 | 2k2 | R-RESCUE-BLDC_4-HSWR-V2-rescue | Resistor_SMD:R_0805_2012Metric | A129545CT-ND | 3.4000000000000002E-2 |  | 0.17
R6, R5, R30, | 3 | 120R | R_Small-Device | Resistor_SMD:R_0805_2012Metric | RHM120KCT-ND | 8.3000000000000004E-2 |  | 0.249
R7, R53, R55, R57, | 4 | 220k | R-RESCUE-BLDC_4-HSWR-V2-rescue | Resistor_SMD:R_0805_2012Metric | RHM220KKCT-ND | 8.3000000000000004E-2 |  | 0.33200000000000002
R8, R54, R56, R58, | 4 | 3k3 | R-RESCUE-BLDC_4-HSWR-V2-rescue | Resistor_SMD:R_0805_2012Metric | A126440CT-ND | 7.0000000000000007E-2 |  | 0.28000000000000003
R9, | 1 | NTC 10k | R-RESCUE-BLDC_4-HSWR-V2-rescue | Resistor_SMD:R_0603_1608Metric | 490-18149-1-ND | 8.3000000000000004E-2 |  | 8.3000000000000004E-2
R18, R10, R32, R38, R37, R36, R77, | 7 | 10k 1% | R-Device | Resistor_SMD:R_0805_2012Metric | RNCP0805FTD10K0CT-ND | 7.2999999999999995E-2 |  | 0.51100000000000001
R19, R24, | 2 | 68k | R-Device | Resistor_SMD:R_0805_2012Metric | RHM68KKCT-ND | 8.4000000000000005E-2 |  | 0.16800000000000001
R29, R23, R22, R17, R16, R14, R15, R20, R21, R27, R28, R26, | 12 | 1R | R-Device | Resistor_SMD:R_0805_2012Metric | RNCP0805FTD1R00CT-ND | 2.7E-2 |  | 0.32400000000000001
R31, | 1 | 300R 750mw | R_Small-Device | Resistor_SMD:R_1206_3216Metric | 541-300UACT-ND | 0.42 |  | 0.42
R39, | 1 | 28k | R-Device | Resistor_SMD:R_0805_2012Metric | RNCP0805FTD28K0CT-ND | 2.8000000000000001E-2 |  | 2.8000000000000001E-2
R40, | 1 | 100k | R-Device | Resistor_SMD:R_0805_2012Metric | A126415CT-ND | 7.0000000000000007E-2 |  | 7.0000000000000007E-2
R41, | 1 | 110k | R-Device | Resistor_SMD:R_0805_2012Metric | RMCF0805FT110KCT-ND | 0.1 |  | 0.1
R42, | 1 | 15k | R-Device | Resistor_SMD:R_0805_2012Metric | RNCP0805FTD15K0CT-ND | 7.1999999999999995E-2 |  | 7.1999999999999995E-2
R43, | 1 | 49k9 | R-Device | Resistor_SMD:R_0805_2012Metric | RNCP0805FTD49K9CT-ND | 7.1999999999999995E-2 |  | 7.1999999999999995E-2
R44, | 1 | 11k | R-Device | Resistor_SMD:R_0805_2012Metric | RNCP0805FTD11K0CT-ND | 7.1999999999999995E-2 |  | 7.1999999999999995E-2
R48, R47, R45, | 3 | CSS2H-3920R-L500 | R-Device | eigene_mod:CSS3920 | s.r. | 1.75 |  | 5.25 |  | CSS2H-3920R-L200FCT-ND |  | ?X
R52, R60, R59, R51, R25, R50, R49, R46, | 8 | 50k | R-Device | Resistor_SMD:R_0805_2012Metric | 764-1535-1-ND | 0.78 |  | 6.24
R61, | 1 | 442R 1% | R_Small-Device | Resistor_SMD:R_0805_2012Metric | 311-442CRCT-ND | 0.05 |  | 0.05
R64, | 1 | 1K24 1% | R_Small-Device | Resistor_SMD:R_0805_2012Metric | 311-1.24KCRCT-ND |  |  | 0
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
